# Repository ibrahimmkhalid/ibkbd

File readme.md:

# IBKBD
_Ibrahim's Keyboards_

- IBKBD Full
    - Custom physical layout, PCB, Case, and keymap
    - 4x6 + 5 + 3 _(Inspired heavily by [Dygma Defy](https://dygma.com/products/dygma-defy))_
    - Generic DSA keycaps
    - Kailh Midnight Pro Silent Tactile Switches
    - Pro Micro ATmega32U4 with type C port
    - check ./ibkbd-full/ for all relevant files

- IBKBD Mini
    - Custom physical layout, PCB, Case, and keymap
    - 3x5 + 3 (Inspired by Absolem and Corne keyboards)
    - DDC Choc keycaps
    - Sunset Tactile Choc Switches
    - NiceNano v2
    - check ./ibkbd-mini/ for all relevant files

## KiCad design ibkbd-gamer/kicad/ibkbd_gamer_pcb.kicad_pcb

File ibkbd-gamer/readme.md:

# IBKBD

_Ibrahim's Gamer Mode Keyboard_

- 4x6 + 6 + 3

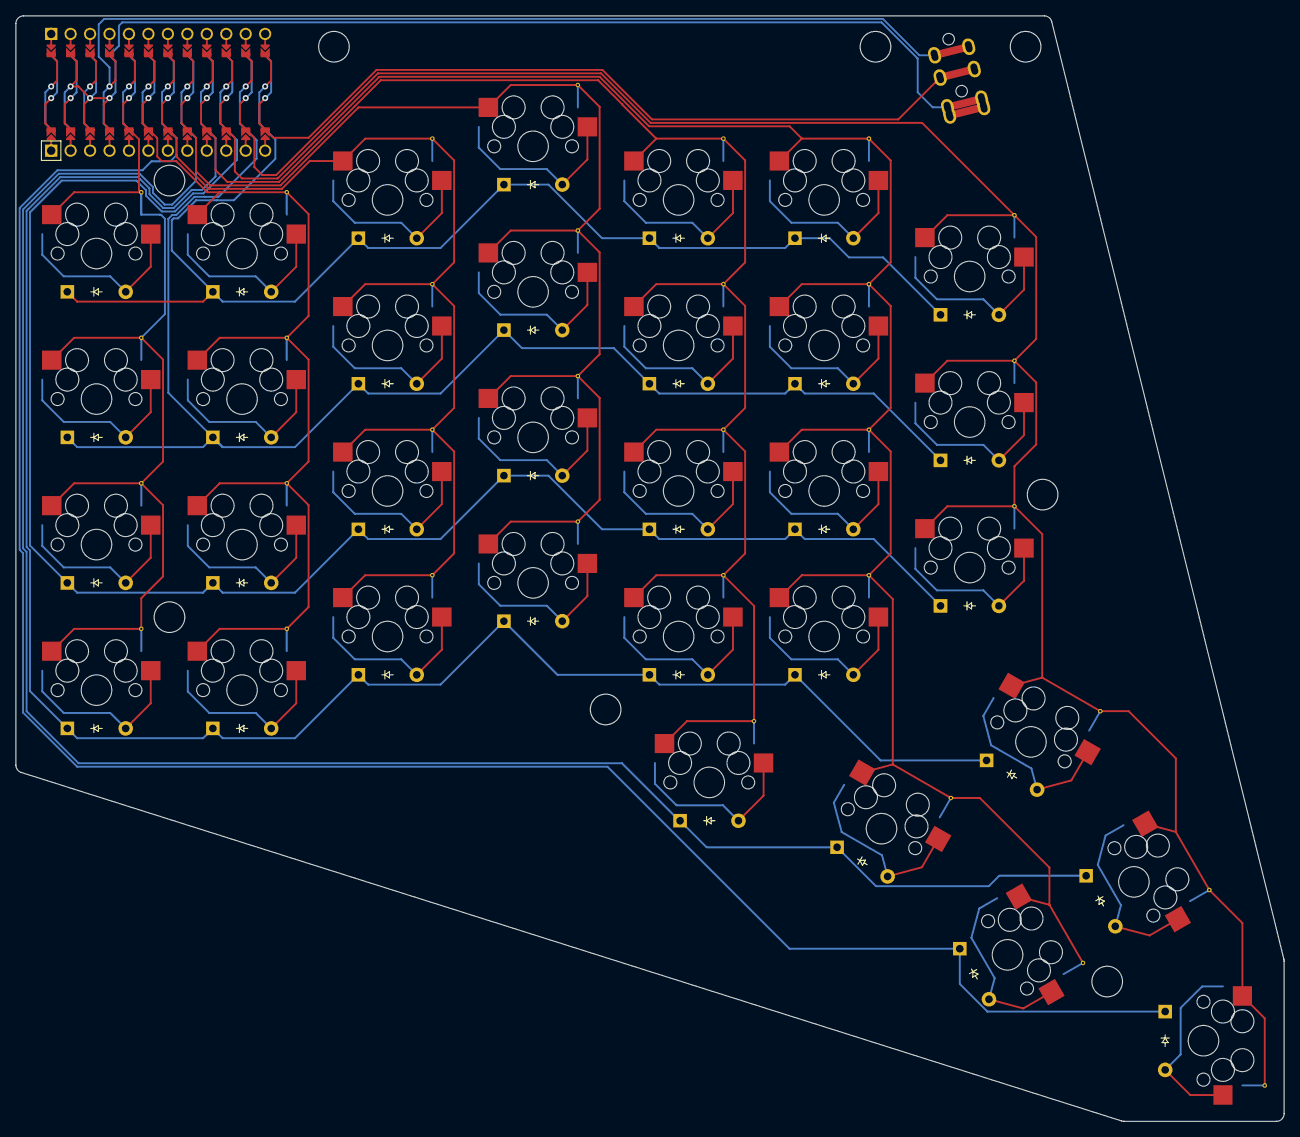
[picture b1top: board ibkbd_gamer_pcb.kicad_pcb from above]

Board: 2 copper layers, 165.6 x 144.3 mm, 35 parts (0 on the bottom side), 16 nets.

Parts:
MCU1: ProMicro
S1, S2, S3, S4, S5, S6, S7, S8, S9, S10, S11, S12, S13, S14, S15, S16, S17, S18, S19, S20, S21, S22, S23, S24, S25, S26, S27, S28, S29, S30, S31, S32, S33: MXWD
TRRS1: TRRS-PJ-320A-dual

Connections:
GND: MCU1.2, MCU1.21, MCU1.22, TRRS1.1, TRRS1.2
P2: MCU1.20, S1.1, S2.1, S3.1, S4.1
P3: MCU1.19, S5.1, S6.1, S7.1, S8.1
P4: MCU1.18, S9.1, S10.1, S11.1, S12.1
P5: MCU1.17, S13.1, S14.1, S15.1, S16.1
P6: MCU1.16, S17.1, S18.1, S19.1, S20.1, S28.1
P7: MCU1.15, S21.1, S22.1, S23.1, S24.1, S29.1, S30.1
P8: MCU1.14, S25.1, S26.1, S27.1, S31.1, S32.1, S33.1
P9: MCU1.13, TRRS1.3
P10: MCU1.12, S4.2, S8.2, S12.2, S16.2, S20.2, S24.2, S27.2
P14: MCU1.10, S2.2, S6.2, S10.2, S14.2, S18.2, S22.2, S25.2
P15: MCU1.9, S1.2, S5.2, S9.2, S13.2, S17.2, S21.2, S32.2
P16: MCU1.11, S3.2, S7.2, S11.2, S15.2, S19.2, S23.2, S26.2
P18: MCU1.8, S28.2, S29.2, S31.2
P19: MCU1.7, S30.2, S33.2
VCC: MCU1.4, TRRS1.4

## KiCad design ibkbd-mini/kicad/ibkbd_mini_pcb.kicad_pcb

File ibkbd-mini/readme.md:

# IBKBD

_Ibrahim's Keyboard_

- Custom physical layout, PCB, Case, and keymap
- 3x5 + 3 (Inspired by Absolem and Corne keyboards)
- DDC Choc keycaps
- Sunset Tactile Choc Switches
- NiceNano v2

I wanted to create an ultra portable version of the IBKBD-Full. This version uses low profile choc switches, does not have the gaming layer keys, and is a uni-body design.

#### In this project

- ergogen config
- completed kicad pcb
- generated 3d printing case files
- qmk keymap (substitute NiceNano)
- zmk keymap

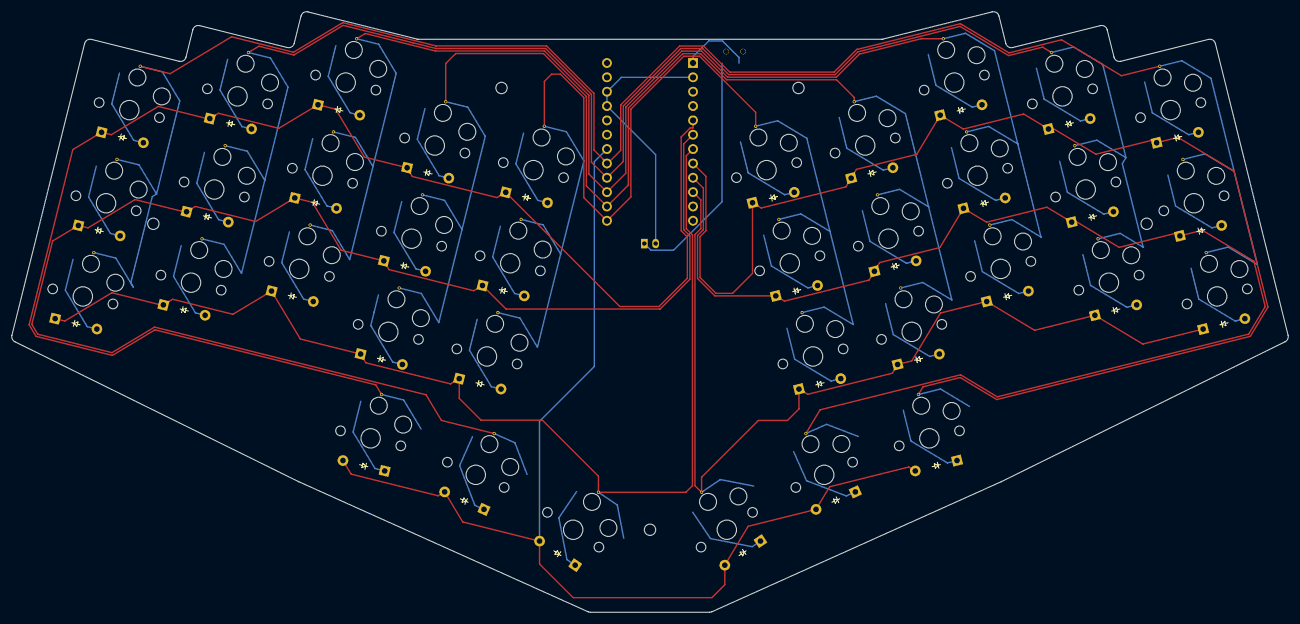
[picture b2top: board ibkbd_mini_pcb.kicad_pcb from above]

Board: 2 copper layers, 226.0 x 106.3 mm, 75 parts (1 on the bottom side), 51 nets.

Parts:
D1, D2, D3, D4, D5, D6, D7, D8, D9, D10, D11, D12, D13, D14, D15, D16, D17, D18, D19, D20, D21, D22, D23, D24, D25, D26, D27, D28, D29, D30, D31, D32, D33, D34, D35, D36: ComboDiode
JST1: JST_PH_S2B-PH-K_02x2.00mm_Angled
MCU1: ProMicro
S1, S2, S3, S4, S5, S6, S7, S8, S9, S10, S11, S12, S13, S14, S15, S16, S17, S18, S19, S20, S21, S22, S23, S24, S25, S26, S27, S28, S29, S30, S31, S32, S33, S34, S35, S36: PG1350
T1: SPDT_C128955

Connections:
GND: JST1.2, MCU1.2, MCU1.15, MCU1.16
P4: D31.2, D32.2, D33.2, D34.2, D35.2, D36.2, MCU1.19
P5: MCU1.20, S1.2, S2.2, S3.2, S16.2, S17.2, S18.2
P6: MCU1.21, S4.2, S5.2, S6.2, S19.2, S20.2, S21.2
P7: MCU1.22, S7.2, S8.2, S9.2, S22.2, S23.2, S24.2
P8: MCU1.23, S10.2, S11.2, S12.2, S25.2, S26.2, S27.2
P9: MCU1.24, S13.2, S14.2, S15.2, S28.2, S29.2, S30.2
P14: D16.1, D19.1, D22.1, D25.1, D28.1, MCU1.10, S36.2
P15: D17.1, D20.1, D23.1, D26.1, D29.1, MCU1.9, S35.2
P18: D18.1, D21.1, D24.1, D27.1, D30.1, MCU1.8, S34.2
P19: D1.1, D4.1, D7.1, D10.1, D13.1, MCU1.7, S33.2
P20: D2.1, D5.1, D8.1, D11.1, D14.1, MCU1.6, S32.2
P21: D3.1, D6.1, D9.1, D12.1, D15.1, MCU1.5, S31.2
RAW: MCU1.1, T1.2
batswitch: JST1.1, T1.1
index_bottom: D10.2, S10.1
index_home: D11.2, S11.1
index_top: D12.2, S12.1
inner_bottom: D13.2, S13.1
inner_home: D14.2, S14.1
inner_key: D31.1, S31.1
inner_top: D15.2, S15.1
mid_key: D32.1, S32.1
middle_bottom: D7.2, S7.1
middle_home: D8.2, S8.1
middle_top: D9.2, S9.1
mirror_index_bottom: D25.2, S25.1
mirror_index_home: D26.2, S26.1
mirror_index_top: D27.2, S27.1
mirror_inner_bottom: D28.2, S28.1
mirror_inner_home: D29.2, S29.1
mirror_inner_key: D34.1, S34.1
mirror_inner_top: D30.2, S30.1
mirror_mid_key: D35.1, S35.1
mirror_middle_bottom: D22.2, S22.1
mirror_middle_home: D23.2, S23.1
mirror_middle_top: D24.2, S24.1
mirror_outer_key: D36.1, S36.1
mirror_pinky_bottom: D16.2, S16.1
mirror_pinky_home: D17.2, S17.1
mirror_pinky_top: D18.2, S18.1
mirror_ring_bottom: D19.2, S19.1
mirror_ring_home: D20.2, S20.1
mirror_ring_top: D21.2, S21.1
outer_key: D33.1, S33.1
pinky_bottom: D1.2, S1.1
pinky_home: D2.2, S2.1
pinky_top: D3.2, S3.1
ring_bottom: D4.2, S4.1
ring_home: D5.2, S5.1
ring_top: D6.2, S6.1

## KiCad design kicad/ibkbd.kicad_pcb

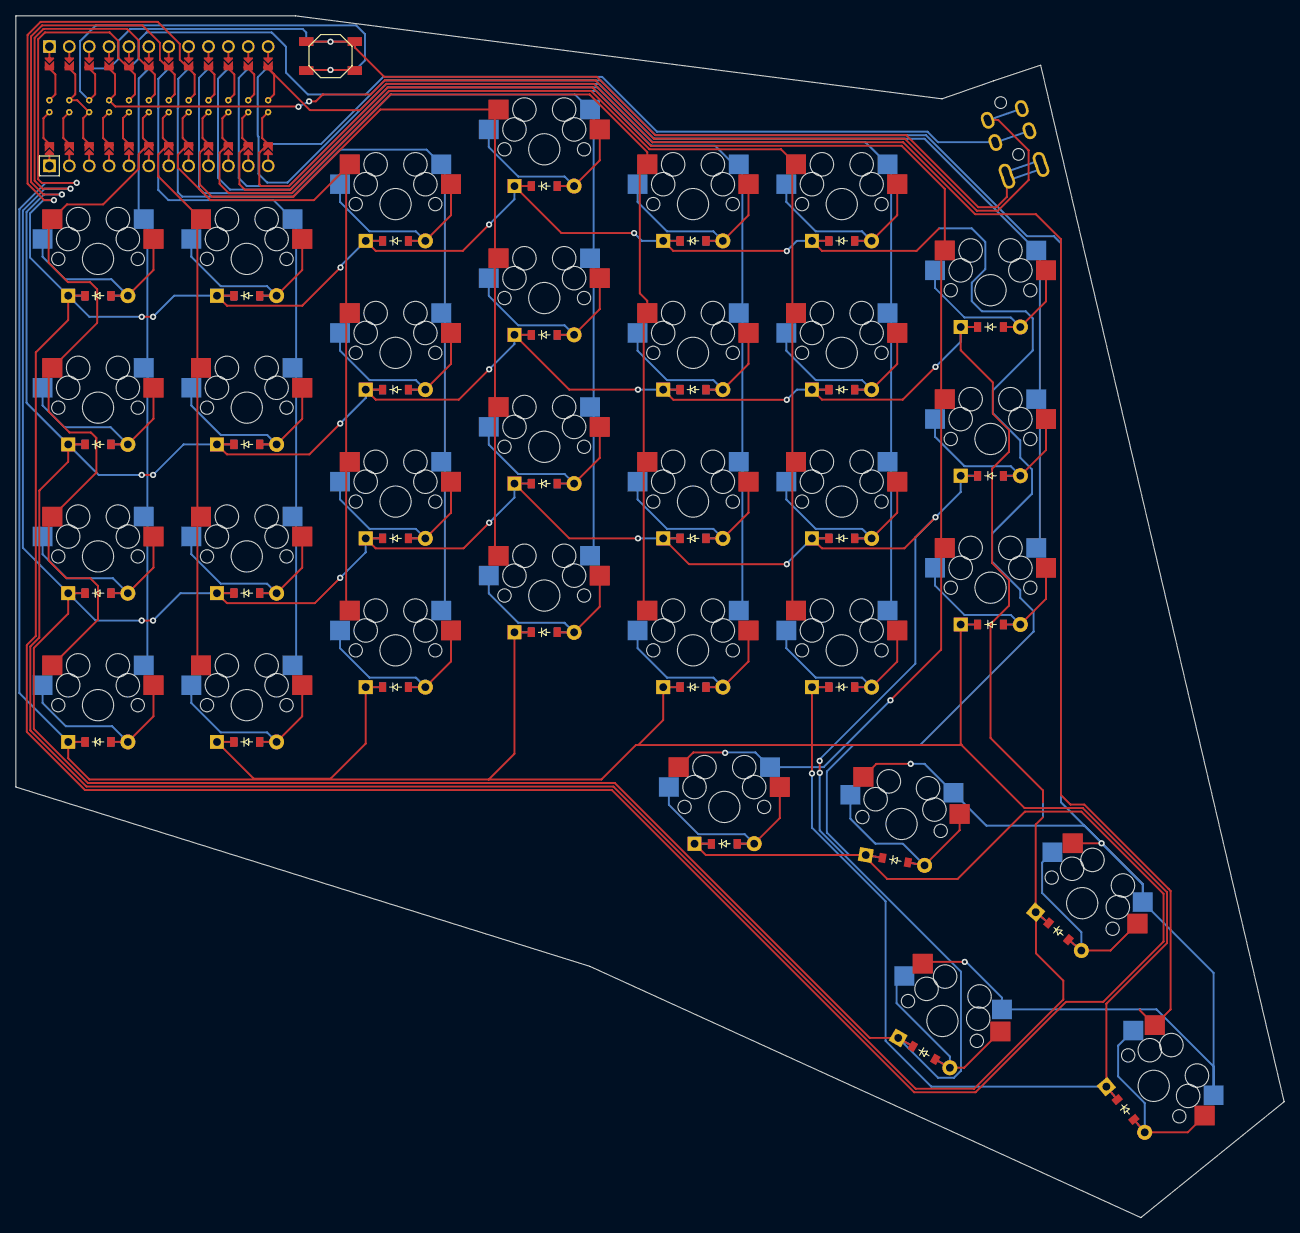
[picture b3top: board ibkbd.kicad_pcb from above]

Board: 2 copper layers, 162.0 x 153.5 mm, 67 parts (0 on the bottom side), 46 nets.

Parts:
B1, B2: SW_TACT_ALPS_SKQGABE010
D1, D2, D3, D4, D5, D6, D7, D8, D9, D10, D11, D12, D13, D14, D15, D16, D17, D18, D19, D20, D21, D22, D23, D24, D25, D26, D27, D28, D29, D30, D31, D32: ComboDiode
MCU1: ProMicro
S1, S2, S3, S4, S5, S6, S7, S8, S9, S10, S11, S12, S13, S14, S15, S16, S17, S18, S19, S20, S21, S22, S23, S24, S25, S26, S27, S28, S29, S30, S31, S32: MX

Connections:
GND: B1.2, B2.2, MCU1.2, MCU1.21, MCU1.22
P3: MCU1.19, S1.2, S2.2, S3.2, S4.2
P4: MCU1.18, S5.2, S6.2, S7.2, S8.2
P5: MCU1.17, S9.2, S10.2, S11.2, S12.2
P6: MCU1.16, S13.2, S14.2, S15.2, S16.2
P7: MCU1.15, S17.2, S18.2, S19.2, S20.2
P8: MCU1.14, S21.2, S22.2, S23.2, S24.2
P9: MCU1.13, S25.2, S26.2, S27.2, S28.2
P10: MCU1.12, S29.2, S30.2, S31.2, S32.2
P18: D4.1, D4.2, D8.1, D8.2, D12.1, D12.2, D16.1, D16.2, D20.1, D20.2, D24.1, D24.2, D28.1, D28.2, D29.1, D29.2, MCU1.8
P19: D3.1, D3.2, D7.1, D7.2, D11.1, D11.2, D15.1, D15.2, D19.1, D19.2, D23.1, D23.2, D27.1, D27.2, D30.1, D30.2, MCU1.7
P20: D2.1, D2.2, D6.1, D6.2, D10.1, D10.2, D14.1, D14.2, D18.1, D18.2, D22.1, D22.2, D26.1, D26.2, D31.1, D31.2, MCU1.6
P21: D1.1, D1.2, D5.1, D5.2, D9.1, D9.2, D13.1, D13.2, D17.1, D17.2, D21.1, D21.2, D25.1, D25.2, D32.1, D32.2, MCU1.5
RST: B1.1, B2.1, MCU1.3
extra_bottom: D25.1, D25.2, S25.1
extra_home: D26.1, D26.2, S26.1
extra_top: D27.1, D27.2, S27.1
far_ext: D31.1, D31.2, S31.1
far_ext2: D32.1, D32.2, S32.1
far_thumb: D30.1, D30.2, S30.1
home_thumb: D29.1, D29.2, S29.1
index_bottom: D17.1, D17.2, S17.1
index_home: D18.1, D18.2, S18.1
index_num: D20.1, D20.2, S20.1
index_top: D19.1, D19.2, S19.1
inner_bottom: D21.1, D21.2, S21.1
inner_home: D22.1, D22.2, S22.1
inner_num: D24.1, D24.2, S24.1
inner_top: D23.1, D23.2, S23.1
middle_bottom: D13.1, D13.2, S13.1
middle_home: D14.1, D14.2, S14.1
middle_num: D16.1, D16.2, S16.1
middle_top: D15.1, D15.2, S15.1
near_thumb: D28.1, D28.2, S28.1
outer_bottom: D1.1, D1.2, S1.1
outer_home: D2.1, D2.2, S2.1
outer_num: D4.1, D4.2, S4.1
outer_top: D3.1, D3.2, S3.1
pinky_bottom: D5.1, D5.2, S5.1
pinky_home: D6.1, D6.2, S6.1
pinky_num: D8.1, D8.2, S8.1
pinky_top: D7.1, D7.2, S7.1
ring_bottom: D9.1, D9.2, S9.1
ring_home: D10.1, D10.2, S10.1
ring_num: D12.1, D12.2, S12.1
ring_top: D11.1, D11.2, S11.1

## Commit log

2024-01-10 refactor: move all file to its own subproject allow possible space for more projects
2024-01-10 initial ibkbd mini
2024-01-10 Revert "refactor: move all file to its own subproject"
    This reverts commit 40ac549ca16cb1e7f994a59c04abda420fa7acbc.
2024-01-10 Revert "Revert "refactor: move all file to its own subproject""
    This reverts commit 9ab7bfc7b2d63e8a07769d03e0b0267bc4c02f83.
2024-01-11 add basic outline shape
2024-01-11 add pcb outline
2024-01-11 use choc spacing
2024-01-11 add pcb and fix nets
2024-01-11 local ergogen intsall
2024-01-11 add mounting holes
2024-01-11 use official ergogen and local footprints
2024-01-11 update nets
2024-01-12 add battery and slider switch
2024-01-12 using github action to generate pcb and gerber
2024-01-12 fix typo
2024-01-12 replace failing image
2024-01-12 missed one
2024-01-12 reverting the previous change
2024-01-12 remove github actions
2024-01-12 update pcb name
2024-01-12 modify thumb key placement
2024-01-12 make readable
2024-01-12 dont block screw with mcu
2024-01-13 add case and other minor fixes
2024-01-13 update make script to convert jscad to stl
2024-01-15 overhaul case design
2024-01-16 routed pcb
2024-01-16 rename folder
2024-01-17 reverse diode direction
2024-01-19 add fix for kicad placement
2024-01-19 fix diode direction on thumb keys, update routed pcb
2024-01-24 adding qmk configs
2024-02-02 update pcb to use hotswap choc switches
2024-02-03 udpate tracks and position of slider
2024-02-04 update kicad pcb
2024-02-04 udpate debug view
2024-02-04 update mount hole position to accomodate hotswap sockets
2024-02-04 add keycaps to debug view
2024-02-15 refactor
2024-05-27 add radii
2024-05-28 add keymap svg using keyboard drawer
2024-06-02 mini:update 3D specifications
2024-06-05 mini: udpate bottom plate
2024-06-13 mini: clean up pcb
2024-06-15 mini: add zmk
2024-06-16 update zmk
2024-06-22 mini: flip mcu to correct side up
2024-06-22 mini: update zmk
2024-06-22 auto formatting
2024-06-22 fix standoff holes
2024-07-25 add shifted gaming compatibility layer
2024-08-09 update image
2024-08-14 remove old files
2025-05-19 prog
2025-05-19 make new kind
2025-05-19 add 6th thumb
2025-05-19 added cases commented
2025-05-19 fix angle
2025-05-19 add _pcb_drill, still needs refinement
2025-05-19 add pcb, still needs refinement
2025-05-19 make promicro w and l controllable
2025-05-19 remove cx,cy
2025-05-19 adjust thumb keys
2025-05-19 make main block
2025-05-20 promicro placements
2025-05-21 tentative complete case
2025-05-21 place trrs
2025-05-21 fix standoff positions
2025-05-21 make reversable pcb
2025-05-21 i dont remember why i did this so im just gonna remove it 🤷
2025-05-21 reversible promicro
2025-05-21 remove via
2025-05-21 not needed
2025-05-21 added extra screw
2025-05-21 fix KiCad placement
2025-05-22 nets
2025-05-22 cleanup
2025-05-22 add via
2025-05-22 create unified footprint
2025-05-22 fix traces in footprint
2025-05-22 unrouted final pcb
2025-05-22 case files
    tentative
    top plate needs to be mirrored when printing
2025-05-30 update pcb
2025-06-01 cleanup yaml
2025-06-01 make cutout in bottom_plate for _trrs_slot
2025-06-01 make reverse standoffs
2025-06-01 Revert "make reverse standoffs"
    This reverts commit e2e1922b3e0b0666c3336e85e830020ad5ffaf08.
2025-06-01 qmk incomplete fix later do not use as is
2025-06-04 move to through hole design
2025-06-04 cleanup config.yaml
2025-06-15 copy stuff over
2025-06-16 did stuff
    keys, outline, pcb, footprints
2025-10-13 add wip indicators
